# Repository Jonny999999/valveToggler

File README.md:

# ValveToggler-24V (Pneumatic Dust Filter Shaker)
Small analog controller PCB that drives a **5/3 pneumatic valve (2 coils)** to shake dust filters of a wood-chip extraction system (*Holzspäne-Absaugung*).  

*Motivation:* Take switching stress off a LOGO! PLC's **relay outputs** (high-frequency switching, inductive load, continuous use over years) by moving the coil drive to **MOSFETs** and hardware timers. The PLC now only provides **high-impedance continuous signals** to enable/disable the shaking in the desired mode.

---

## System Hardware
- **24 V DC** supply (same rail as valve coils)
- **5/3-way pneumatic valve** with two **24 V** coils
- **Double acting pneumatic cylinder** shaking the filters
- **Mechanical stops** at cylinder's limits for abrupt stop so the dust falls off
- Two PLC control lines: `MODE_SINGLE_24V`, `MODE_DOUBLE_24V` (double has priority)

## PCB Features
- Steps **24 V** mode lines to **12 V**, generates timing with 2x **NE555**
- **Modes & timing**  
  - **SINGLE:** Toggle Coil1 only, with independent **ON/OFF** time (typ. ~300 ms ON, ~1.0 s OFF)  
     Adjustable range ≈ **70 – 400 ms** / **0.1 – 3 s**
  - **DOUBLE:** **50 % duty**, **complementary** coil drive (COIL1 = ¬COIL2)  
     Half-period adjustable from **50 ms to 3 s**
- **Low-side N-MOSFET** drivers, flyback/TVS, indicator LEDs
- Input priority & interlock to prevent both coils ON

---

## Files
- **[Schematic (PDF)](export/ValveToggler_schematic.pdf)**
- **[Layout (PNG)](export/ValveToggler_layout.jpg)**

## Schematic + layout preview:  
<p align="center">

</p>

## Photos
Milling and Soldering:
<p align="center">

</p>

<br>

3D-Model and Finished pcb:
<p align="center">

</p>

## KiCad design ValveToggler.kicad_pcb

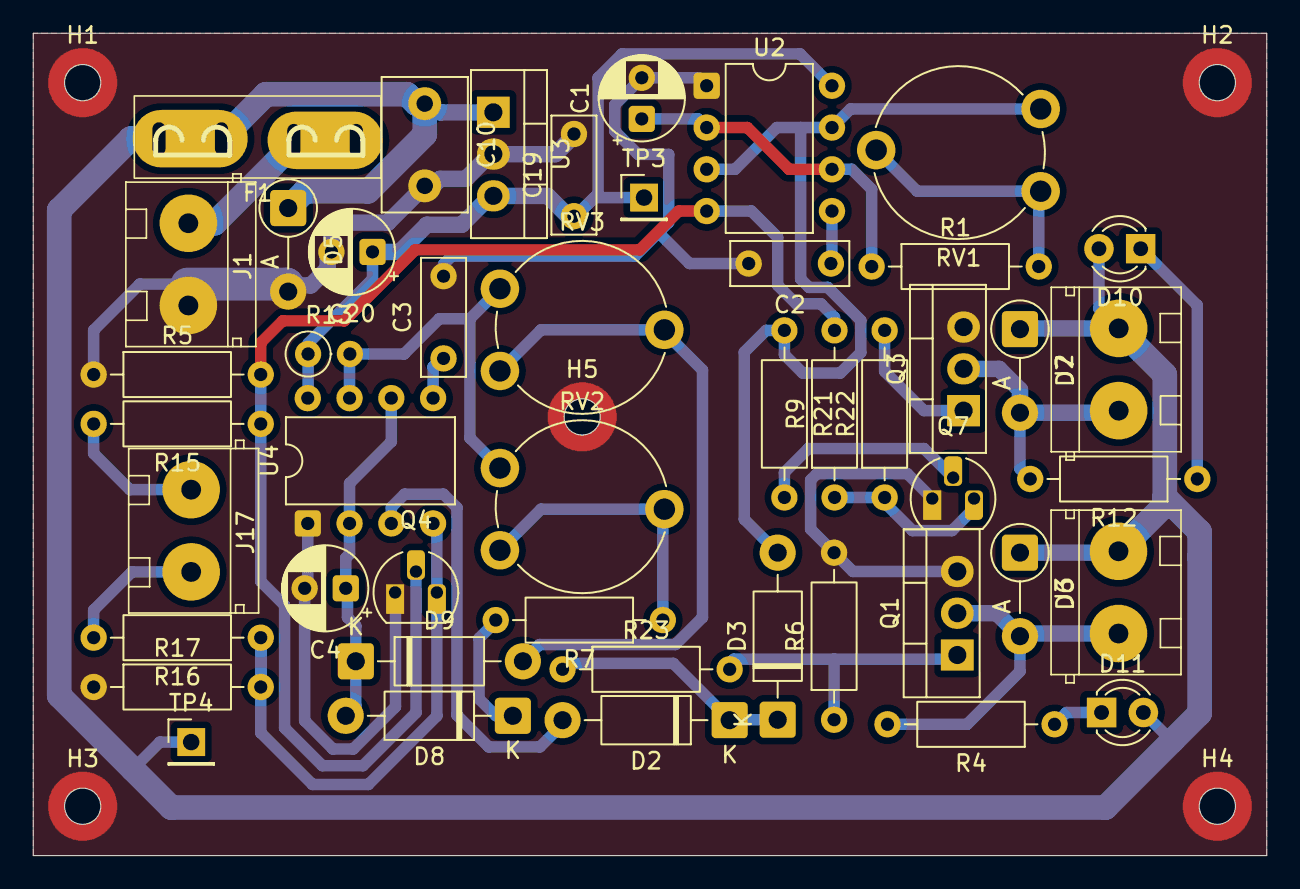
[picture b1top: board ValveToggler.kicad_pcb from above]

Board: 4 copper layers, 75.0 x 50.0 mm, 52 parts (0 on the bottom side), 28 nets.

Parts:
C1, C4, C20: 47u; CP_Radial_D5.0mm_P2.50mm
C2, C3, C19: 100nF; C_Disc_D7.0mm_W2.5mm_P5.00mm
C10: 330nF; C_Disc_D8.0mm_W5.0mm_P5.00mm
D2, D3, D8, D9: 1N5817; D_DO-41_SOD81_P10.16mm_Horizontal
D5, D6, D7: D; D_DO-41_SOD81_P5.08mm_Vertical_AnodeUp
D10: LED2_orange; LED_D3.0mm_Clear
D11: LED1_green; LED_D3.0mm_Clear
F1: slow, max 4A; Fuseholder_Automotive-Mini_Fuse11x4x16_Footprint15x5_Inline
H1, H2, H3, H4, H5: MountingHole_Pad; MountingHole_2.2mm_NPTH-with-pad_DRC-clearance-error
J1: 24V IN; ScrewTerminal_P5mm_2Pin_FP10x8
J2: Coil2; ScrewTerminal_P5mm_2Pin_FP10x8
J3: Coil1; ScrewTerminal_P5mm_2Pin_FP10x8
J17: MODE (24V); ScrewTerminal_P5mm_2Pin_FP10x8
Q1, Q3: IRFZ24N; TO-220-3_Vertical
Q4, Q7: 2N7000; TO-92_HandSolder
R1: 1k5_f-max; R_Axial_DIN0207_L6.3mm_D2.5mm_P10.16mm_Horizontal
R4, R12: 3k3; R_Axial_DIN0207_L6.3mm_D2.5mm_P10.16mm_Horizontal
R5, R15, R16, R17: 2k2; R_Axial_DIN0207_L6.3mm_D2.5mm_P10.16mm_Horizontal
R6, R9: 10k; R_Axial_DIN0207_L6.3mm_D2.5mm_P10.16mm_Horizontal
R7: 3k3_t-offMin; R_Axial_DIN0207_L6.3mm_D2.5mm_P10.16mm_Horizontal
R13: 2k2_t-onMin; R_Axial_DIN0207_L6.3mm_D2.5mm_P2.54mm_Vertical
R21, R22, R23: 330; R_Axial_DIN0207_L6.3mm_D2.5mm_P10.16mm_Horizontal
RV1: 100k_freq; Potentiometer_Piher_PT-10-V10_Vertical
RV2: 100k_t-off; Potentiometer_Piher_PT-10-V10_Vertical
RV3: 10k_t-on; Potentiometer_Piher_PT-10-V10_Vertical
TP3: 12V; PinHeader_1x01_P2.54mm_Vertical
TP4: 24V; PinHeader_1x01_P2.54mm_Vertical
U2, U4: NE555P; DIP-8_W7.62mm
U3: L7812; TO-220-3_Vertical

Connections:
+12V: C19.1, C20.1, R13.1, TP3.1, U2.8 (VCC), U3.3 (OUT), U4.8 (VCC)
+24V: C10.1, D5.1 (K), D6.1 (K), D7.1 (K), D10.2 (A), D11.2 (A), F1.2, J2.2, J3.2, TP4.1, U3.1 (IN)
/Drain1: D6.2 (A), J3.1, Q1.2 (D), R4.2
/Drain2: D7.2 (A), J2.1, Q3.2 (D), R12.2
/F1_signal-mode1: D2.2 (A), U4.3 (Q)
/F2_signal-mode2: D3.2 (A), R21.1, RV1.1, U2.3 (Q), U2.7 (DIS)
/MODE_DOUBLE_12V: Q4.2 (G), R5.2, R9.2, R15.1, U2.4 (R)
/MODE_DOUBLE_IN: J17.1, R15.2
/MODE_SINGLE_12V: Q4.3 (D), R16.1, R17.2, U4.4 (R)
/MODE_SINGLE_IN: J17.2, R16.2
/MOS1: D2.1 (K), D3.1 (K), R23.1
/MOS2: Q7.3 (D), R9.1, R22.1
GND: C1.2, C2.2, C3.2, C4.2, C10.2, C19.2, C20.2, D5.2 (A), H1.1, H2.1, H3.1, H4.1, H5.1, J1.2, Q1.3 (S), Q3.3 (S), Q4.1 (S), Q7.1 (S), R5.1, R6.2, R17.1, U2.1 (GND), U3.2 (GND), U4.1 (GND)
unnamed: C4.1, D8.2 (A), D9.1 (K), U4.2 (TR), U4.6 (THR)
unnamed: D8.1 (K), R7.2
unnamed: D9.2 (A), RV3.1, RV3.2
unnamed: D10.1 (K), R12.1
unnamed: D11.1 (K), R4.1
unnamed: F1.1, J1.1
unnamed: Q1.1 (G), R6.1, R23.2
unnamed: Q3.1 (G), R22.2
unnamed: Q7.2 (G), R21.2
unnamed: R1.2, RV1.2, RV1.3
unnamed: R7.1, RV2.1, RV2.2
unnamed: C2.1, U2.5 (CV)
unnamed: C1.1, R1.1, U2.2 (TR), U2.6 (THR)
unnamed: C3.1, U4.5 (CV)
unnamed: R13.2, RV2.3, RV3.3, U4.7 (DIS)

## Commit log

2025-09-10 init - pcb schematic: timer tested, logic wip
2025-09-10 Rework logic (drop PNP, default on coil, pulldown-OR)
2025-09-11 Optimize logic (more current, but significantly fewer parts)
2025-09-11 Layout: Arrange footprints, start poc routing
2025-09-12 Routing complete, DRC pass
2025-09-14 Add R to trimmer (offMin), rework routing, Add timing calculation notes
2025-09-14 Add pcb2gcode script + config from gate repo (pcb_isolated-gate-control)
2025-09-15 Final adjustments pre milling: Mounthole, Text layer, Text thickness
2025-09-17 Arrange Fab text, Update actually soldered Values, Add milled gerber export
2025-09-17 Add README, photos, schematic export
2025-09-18 Fix mos1 not turning fully on (rework leds), Fix swapped text, Add changelog
2025-09-18 Update exports (schematic, layouy, gerber), Add final photo
2025-09-28 Add photo of installed pcb
